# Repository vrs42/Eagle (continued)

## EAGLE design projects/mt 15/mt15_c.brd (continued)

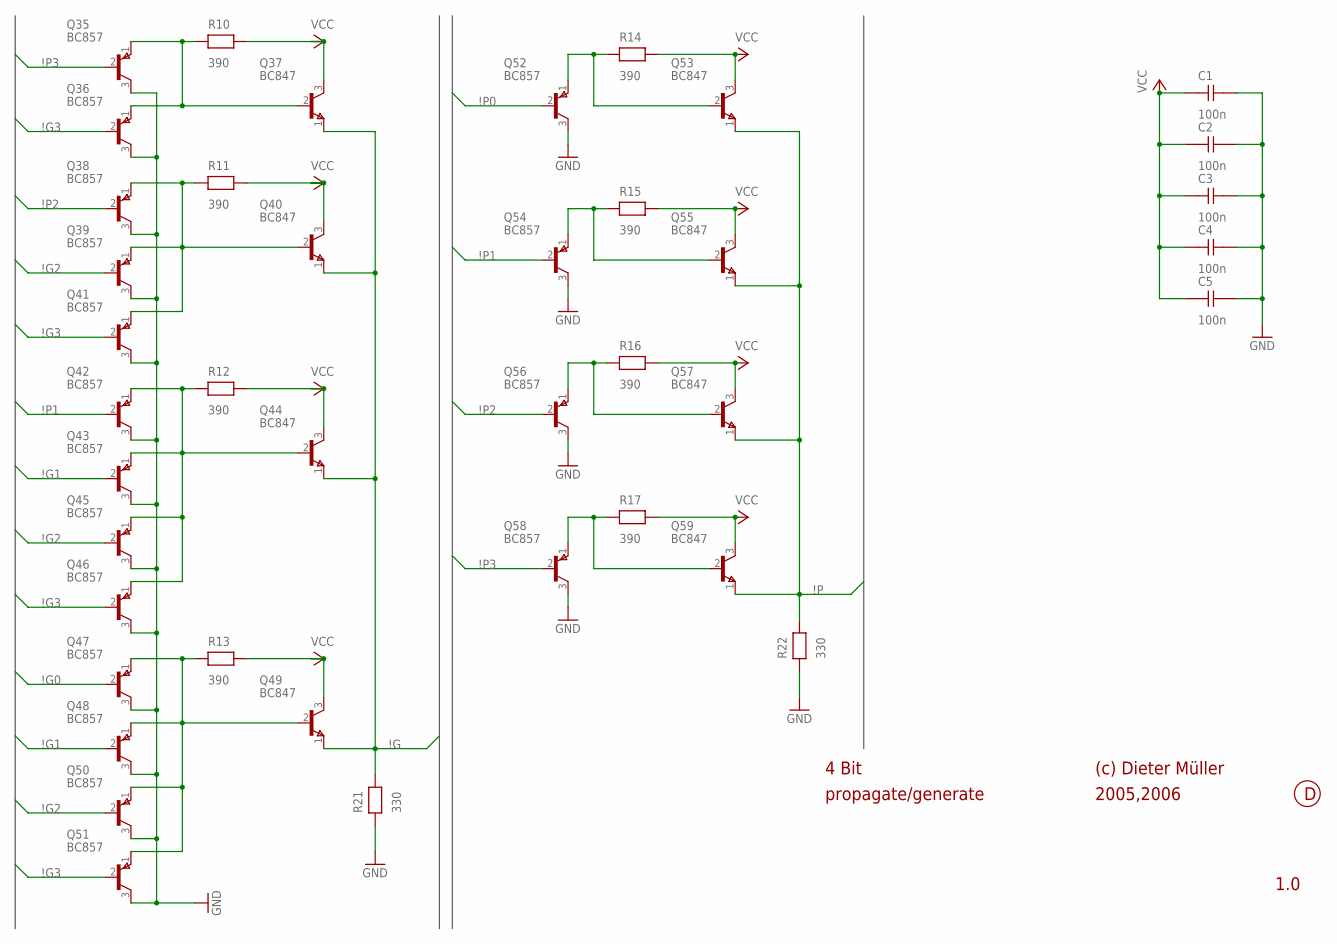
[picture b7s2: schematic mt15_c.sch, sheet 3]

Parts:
C1, C2, C3, C4, C5: 100n; 0204
Q35, Q36, Q38, Q39, Q41, Q42, Q43, Q45, Q46, Q47, Q48, Q50, Q51, Q52, Q54, Q56, Q58: BC857; SOT-23
Q37, Q40, Q44, Q49, Q53, Q55, Q57, Q59: BC847; SOT-23
R10, R11, R12, R13, R14, R15, R16, R17: 390; 0204
R21, R22: 330; 0204

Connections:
GND: C1.2, C2.2, C3.2, C4.2, C5.2, Q35.3 (C), Q36.3 (C), Q38.3 (C), Q39.3 (C), Q41.3 (C), Q42.3 (C), Q43.3 (C), Q45.3 (C), Q46.3 (C), Q47.3 (C), Q48.3 (C), Q50.3 (C), Q51.3 (C), Q52.3 (C), Q54.3 (C), Q56.3 (C), Q58.3 (C), R21.1, R22.1; also elsewhere on the board
unnamed: Q35.1 (E), Q36.1 (E), Q37.2 (B), R10.1
unnamed: Q38.1 (E), Q39.1 (E), Q40.2 (B), Q41.1 (E), R11.1
unnamed: Q42.1 (E), Q43.1 (E), Q44.2 (B), Q45.1 (E), Q46.1 (E), R12.1
unnamed: Q47.1 (E), Q48.1 (E), Q49.2 (B), Q50.1 (E), Q51.1 (E), R13.1
unnamed: Q52.1 (E), Q53.2 (B), R14.1
unnamed: Q54.1 (E), Q55.2 (B), R15.1
unnamed: Q56.1 (E), Q57.2 (B), R16.1
unnamed: Q58.1 (E), Q59.2 (B), R17.1
VCC: C1.1, C2.1, C3.1, C4.1, C5.1, Q37.3 (C), Q40.3 (C), Q44.3 (C), Q49.3 (C), Q53.3 (C), Q55.3 (C), Q57.3 (C), Q59.3 (C), R10.2, R11.2, R12.2, R13.2, R14.2, R15.2, R16.2, R17.2; also elsewhere on the board
\!G: Q37.1 (E), Q40.1 (E), Q44.1 (E), Q49.1 (E), R21.2
\!G0: Q47.2 (B); also elsewhere on the board
\!G1: Q43.2 (B), Q48.2 (B); also elsewhere on the board
\!G2: Q39.2 (B), Q45.2 (B), Q50.2 (B); also elsewhere on the board
\!G3: Q36.2 (B), Q41.2 (B), Q46.2 (B), Q51.2 (B)
\!P: Q53.1 (E), Q55.1 (E), Q57.1 (E), Q59.1 (E), R22.2
\!P0: Q52.2 (B); also elsewhere on the board
\!P1: Q42.2 (B), Q54.2 (B); also elsewhere on the board
\!P2: Q38.2 (B), Q56.2 (B); also elsewhere on the board
\!P3: Q35.2 (B), Q58.2 (B)

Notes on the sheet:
(c) Dieter Müller
2005,2006
1.0
4 Bit
propagate/generate

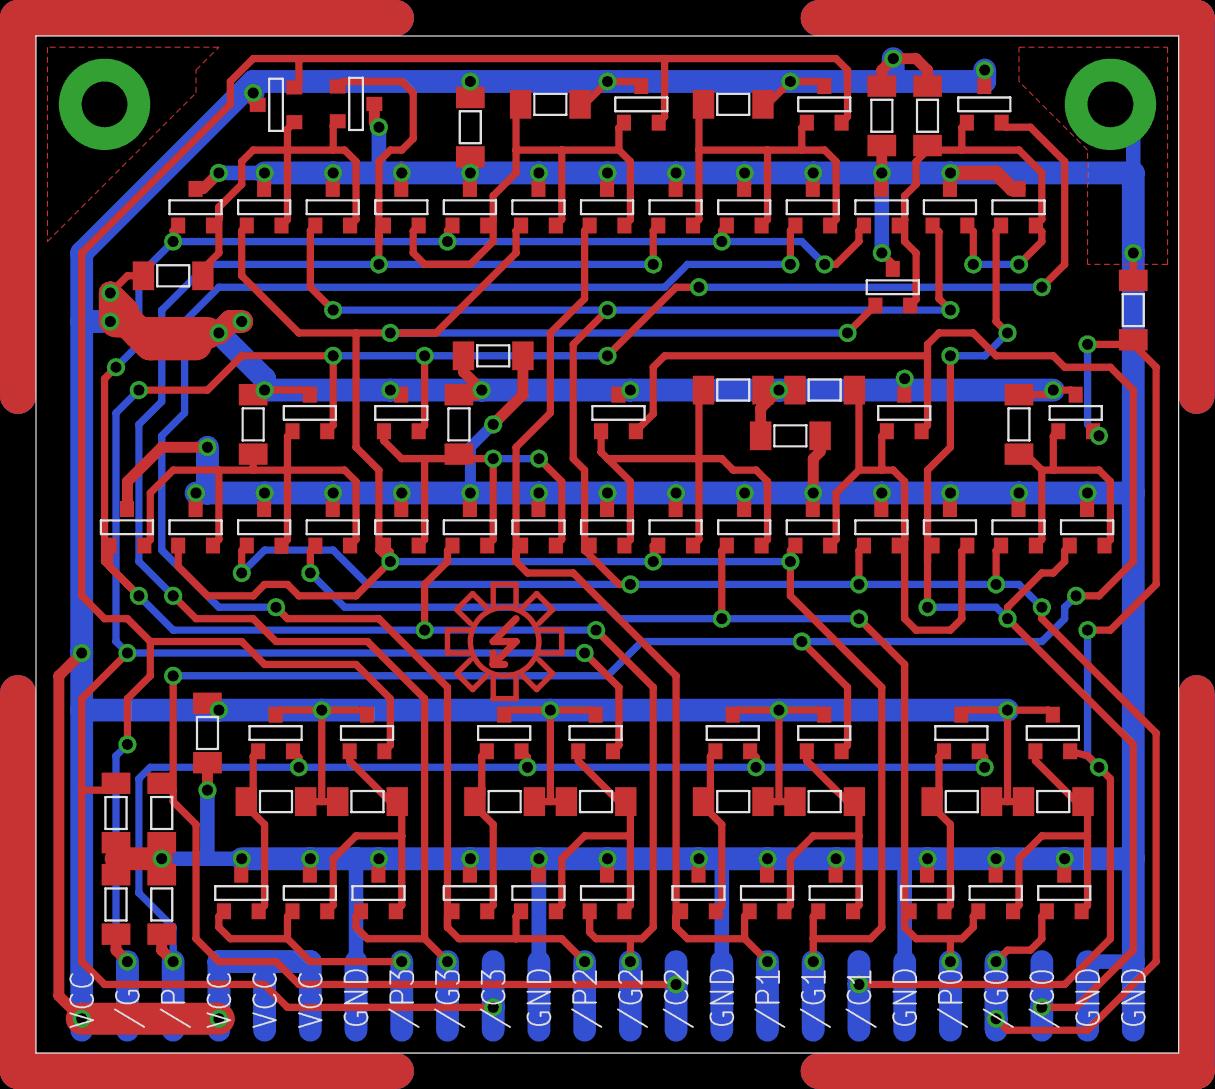
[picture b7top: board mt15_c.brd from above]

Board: 2 copper layers, 63.5 x 56.5 mm, 87 parts (0 on the bottom side), 33 nets.

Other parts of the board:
U$46: T1
